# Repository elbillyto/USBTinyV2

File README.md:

# USBTinyV2
schematics and board designed using 
Kicad Version: (2014-jul-16 BZR unknown)-product Release build
wxWidgets: Version 3.0.1 (debug,wchar_t,compiler with C++ ABI 1002,GCC 4.8.2,wx containers,compatible with 2.8)
Platform: Linux 3.13.0-48-generic i686, 32 bit, Little endian, wxGTK
Boost version: 1.54.0
         USE_WX_GRAPHICS_CONTEXT=OFF
         USE_WX_OVERLAY=OFF
         KICAD_SCRIPTING=ON
         KICAD_SCRIPTING_MODULES=ON
         KICAD_SCRIPTING_WXPYTHON=ON
         USE_FP_LIB_TABLE=HARD_CODED_ON
         BUILD_GITHUB_PLUGIN=ON

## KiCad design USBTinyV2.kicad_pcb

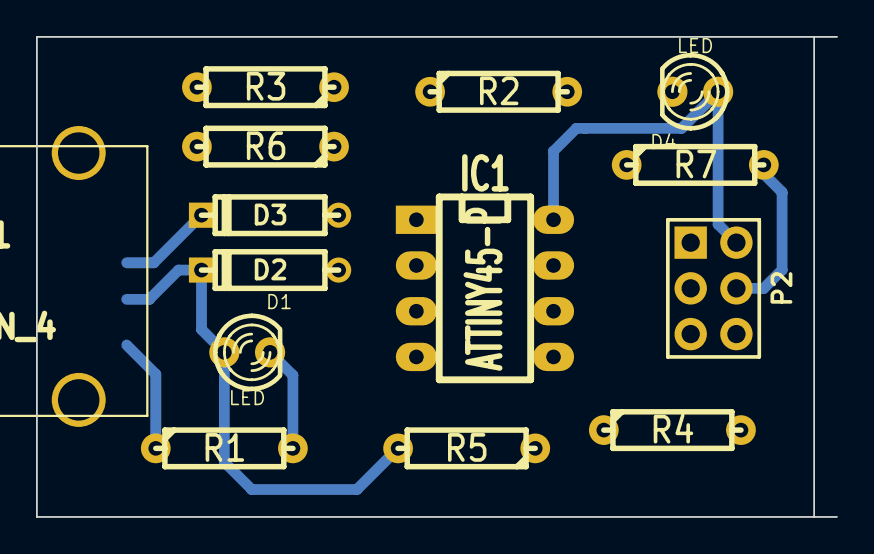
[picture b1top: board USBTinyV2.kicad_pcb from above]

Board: 2 copper layers, 44.5 x 26.7 mm, 14 parts (0 on the bottom side), 14 nets.

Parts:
D1, D4: LED; LED-3MM
D2, D3: 3.6; D3
IC1: ATTINY45-P; DIP-8__300_ELL
P1: CONN_4; USB_A
P2: CONN_3X2; pin_array_3x2
R1: 330; R3-LARGE_PADS
R2: 220; R3-LARGE_PADS
R3, R4, R7: 1.5K; R3-LARGE_PADS
R5, R6: 27; R3-LARGE_PADS

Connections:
+5V: D4.1, IC1.8, P1.1, P2.2, R3.1
/MISO: IC1.6, P2.1
/MOSI: P2.4, R7.2
/RST: IC1.1, P2.e
/SCK: P2.3, R4.2
GND: D2.1, D3.1, IC1.4, P1.4, P2.6, R1.1, R2.1
unnamed: D1.1, D2.2, P1.3, R5.2
unnamed: D1.2, R1.2
unnamed: D3.2, P1.2, R3.2, R6.2
unnamed: D4.2, R2.2
unnamed: IC1.2, R5.1
unnamed: IC1.3, R6.1
unnamed: IC1.5, R7.1
unnamed: IC1.7, R4.1

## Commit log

2015-04-07 Update README.md
    with kicad
